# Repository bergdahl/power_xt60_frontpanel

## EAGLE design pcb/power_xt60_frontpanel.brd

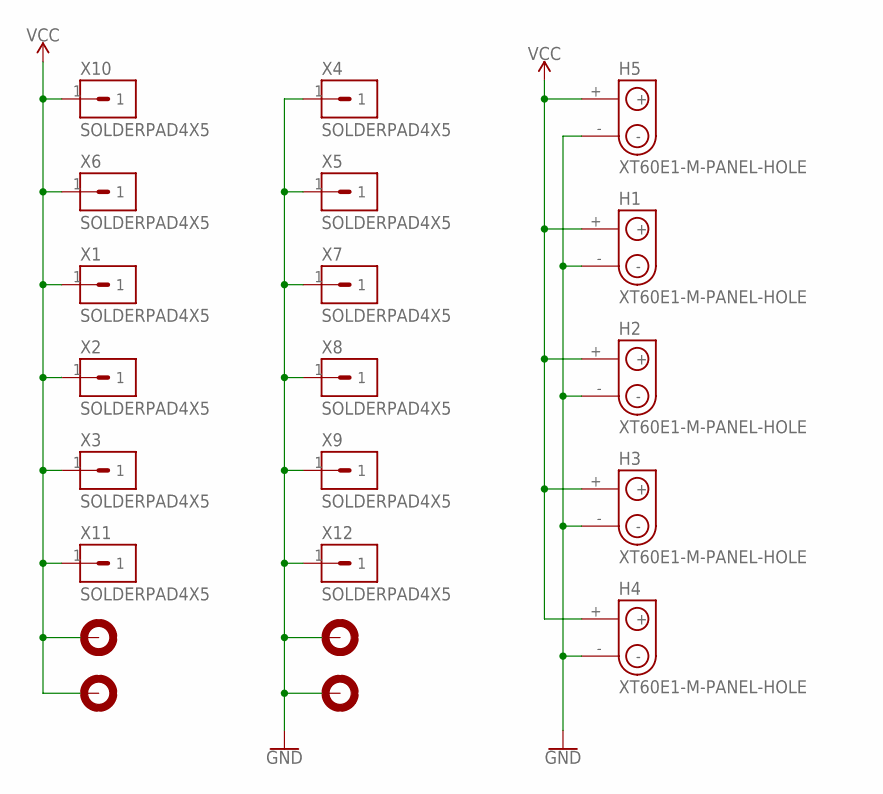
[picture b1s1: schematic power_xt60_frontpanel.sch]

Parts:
H1, H2, H3, H4, H5: XT60E1-M-PANEL-HOLE
H6, H7, H8, H9: MOUNTHOLE-PAD3.2; 3.2-PAD
X1, X2, X3, X4, X5, X6, X7, X8, X9, X10, X11, X12: SOLDERPAD4X5; SOLDERPAD-4X5

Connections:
GND: H1.-, H2.-, H3.-, H4.-, H5.-, H8.B3,2, H9.B3,2, X4.1, X5.1, X7.1, X8.1, X9.1, X12.1
VCC: H1.+, H2.+, H3.+, H4.+, H5.+, H6.B3,2, H7.B3,2, X1.1, X2.1, X3.1, X6.1, X10.1, X11.1

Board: 2 copper layers, 21 parts (12 on the bottom side), 2 nets, no tracks yet.

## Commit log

2021-09-28 Fix alignment
2021-10-11 Revison 2
